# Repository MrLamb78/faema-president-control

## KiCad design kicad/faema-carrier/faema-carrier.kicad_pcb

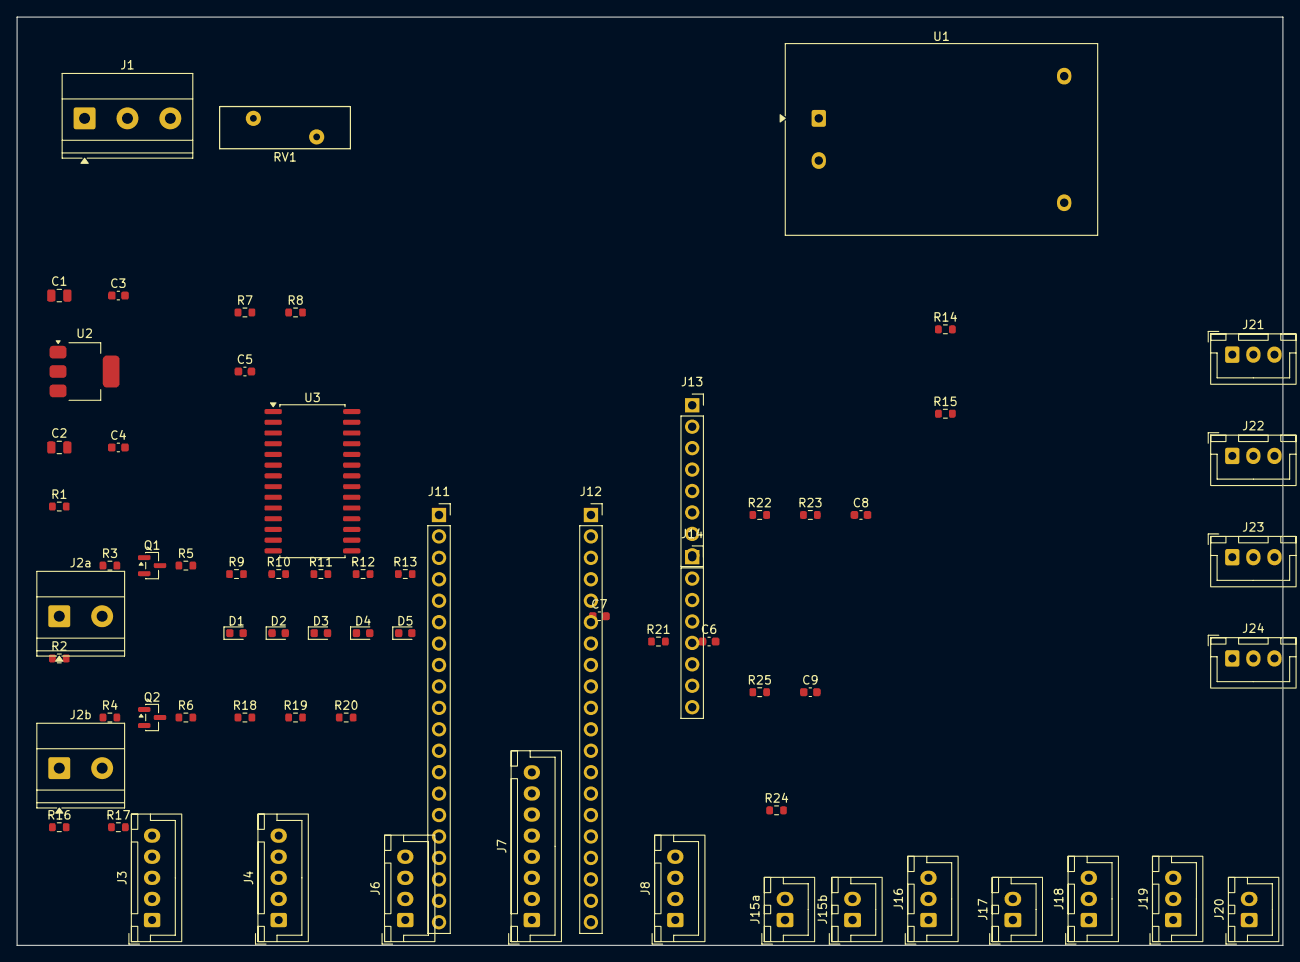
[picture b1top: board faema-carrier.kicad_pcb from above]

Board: 2 copper layers, 150.0 x 110.0 mm, 68 parts (0 on the bottom side), 59 nets, no tracks yet.

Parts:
C1, C2: 10uF_16V; C_0805_2012Metric
C3, C4, C5, C6, C7, C8: 100nF_50V; C_0603_1608Metric
C9: 10nF; C_0603_1608Metric
D1, D2, D3, D4, D5: GREEN; LED_0603_1608Metric
J1: AC_INPUT_220V; TerminalBlock_Phoenix_MKDS-1,5-3-5.08_1x03_P5.08mm_Horizont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
J2a: SSR1_OUT; TerminalBlock_Phoenix_MKDS-1,5-2-5.08_1x02_P5.08mm_Horizont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
J2b: SSR2_OUT; TerminalBlock_Phoenix_MKDS-1,5-2-5.08_1x02_P5.08mm_Horizont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
J3: ENCODER; JST_XH_B5B-XH-A_1x05_P2.50mm_Vertical
J4: BUTTONS; JST_XH_B5B-XH-A_1x05_P2.50mm_Vertical
J6: NEXTION; JST_XH_B4B-XH-A_1x04_P2.50mm_Vertical
J7: SPI_DISPLAY; JST_XH_B8B-XH-A_1x08_P2.50mm_Vertical
J8: I2C_RTC; JST_XH_B4B-XH-A_1x04_P2.50mm_Vertical
J11: PICO_L; PinSocket_1x20_P2.54mm_Vertical
J12: PICO_R; PinSocket_1x20_P2.54mm_Vertical
J13: RTD1; PinSocket_1x08_P2.54mm_Vertical
J14: RTD2; PinSocket_1x08_P2.54mm_Vertical
J15a: LEVEL1; JST_XH_B2B-XH-A_1x02_P2.50mm_Vertical
J15b: LEVEL2; JST_XH_B2B-XH-A_1x02_P2.50mm_Vertical
J16: FLOW; JST_XH_B3B-XH-A_1x03_P2.50mm_Vertical
J17: TEMP_AUX; JST_XH_B2B-XH-A_1x02_P2.50mm_Vertical
J18: PRESSURE; JST_XH_B3B-XH-A_1x03_P2.50mm_Vertical
J19: ANALOG_IN; JST_XH_B3B-XH-A_1x03_P2.50mm_Vertical
J20: PUMP_CTRL; JST_XH_B2B-XH-A_1x02_P2.50mm_Vertical
J21: OUT1; JST_XH_B3B-XH-A_1x03_P2.50mm_Vertical
J22: OUT2; JST_XH_B3B-XH-A_1x03_P2.50mm_Vertical
J23: OUT3; JST_XH_B3B-XH-A_1x03_P2.50mm_Vertical
J24: OUT4; JST_XH_B3B-XH-A_1x03_P2.50mm_Vertical
Q1, Q2: 2N7002; SOT-23
R1, R2: 220R; R_0603_1608Metric
R3, R4, R24: 100R; R_0603_1608Metric
R5, R6, R16, R18, R19, R20, R25: 10k; R_0603_1608Metric
R7, R8: 4k7; R_0603_1608Metric
R9, R10, R11, R12, R13: 470R; R_0603_1608Metric
R14, R15: 100k; R_0603_1608Metric
R17: 15k; R_0603_1608Metric
R21: 2k2_0.1%; R_0603_1608Metric
R22: 33k; R_0603_1608Metric
R23: 82k; R_0603_1608Metric
RV1: S14K275; RV_Disc_D15.5mm_W5mm_P7.5mm
U1: HLK-PM05; Converter_ACDC_Hi-Link_HLK-PMxx
U2: AMS1117-3.3; SOT-223-3_TabPin2
U3: MCP23017; SOIC-28W_7.5x17.9mm_P1.27mm

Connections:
+3V3: C2.1, C4.1, C5.1, C7.1, J3.4, J7.1, J8.1, J12.15, J13.1, J14.1, J19.1, J21.1, J22.1, J23.1, J24.1, R7.1, R8.1, R14.1, R15.1, R18.1, R19.1, R20.1, R21.1, R25.1, U2.2, U3.9, U3.11, U3.19
+5V: C1.1, C3.1, J6.1, J12.19, J16.1, J18.1, R1.1, R2.1, U1.3, U2.3
AC_L1_FUSED: J1.1, RV1.1, U1.1
AC_L2_FUSED: J1.2, RV1.2, U1.2
ANALOG_IN: J12.14, J19.2
BTN1: J4.1, U3.27
BTN2: J4.2, U3.26
BTN3: J4.3, U3.25
BTN4: J4.4, U3.24
BTN5: J4.5, U3.23
CS_DISP: J7.3, J11.14
CS_RTD1: J11.7, J13.7
CS_RTD2: J11.9, J14.7
DC_DISP: J7.5, J11.15
DISP_LED: J7.8, J11.17
ENC_CLK: J3.1, J12.1, R18.2
ENC_DT: J3.2, J12.2, R19.2
ENC_SW: J3.3, J12.4, R20.2
GATE1_DRIVE: Q1.1, R3.2, R5.1
GATE2_DRIVE: Q2.1, R4.2, R6.1
GND: C1.2, C2.2, C3.2, C4.2, C5.2, C6.2, C7.2, C8.2, C9.2, D1.2, D2.2, D3.2, D4.2, D5.2, J3.5, J6.2, J7.2, J8.2, J11.3, J11.8, J11.13, J11.18, J12.3, J12.8, J12.13, J12.18, J13.2, J14.2, J15a.2, J15b.2, J16.3, J17.2, J18.3, J19.3, J20.2, J21.3, J22.3, J23.3, J24.3, Q1.2, Q2.2, R5.2, R6.2, R17.2, R23.2, U1.4, U2.1, U3.10, U3.14, U3.15, U3.16
I2C_SCL: J8.4, J11.20, R8.2, U3.12
I2C_SDA: J8.3, J11.19, R7.2, U3.13
LED1: R9.1, U3.5
LED1_A: D1.1, R9.2
LED2: R10.1, U3.6
LED2_A: D2.1, R10.2
LED3: R11.1, U3.7
LED3_A: D3.1, R11.2
LED4: R12.1, U3.8
LED4_A: D4.1, R12.2
LED5: R13.1, U3.20
LED5_A: D5.1, R13.2
LEVEL1: J15a.1, R14.2, U3.22
LEVEL2: J15b.1, R15.2, U3.21
MCP_INT: J12.9, U3.17
OUT1: J21.2, U3.1
OUT2: J22.2, U3.2
OUT3: J23.2, U3.3
OUT4: J24.2, U3.4
PRESSURE: C8.1, J12.12, R22.2, R23.1
PRESSURE_RAW: J18.2, R22.1
PULSE_IN: C9.1, J12.7, J16.2, R25.2
PUMP_CTRL: J12.6, R24.1
PUMP_OUT: J20.1, R24.2
RST_DISP: J7.4, J11.16
SPI_MISO: J11.6, J13.5, J14.5
SPI_MOSI: J7.6, J11.5, J11.12, J13.6, J14.6
SPI_SCK: J7.7, J11.4, J11.11, J13.4, J14.4
SSR1_CTRL: J11.10, R3.1
SSR1_CTRL_P: J2a.1, R1.2
SSR1_DRIVE: J2a.2, Q1.3
SSR2_CTRL: J12.5, R4.1
SSR2_CTRL_P: J2b.1, R2.2
SSR2_DRIVE: J2b.2, Q2.3
TEMP_AUX: C6.1, J12.11, J17.1, R21.2
UART_RX: J11.2, R16.2, R17.1
UART_RX_5V: J6.3, R16.1
UART_TX: J6.4, J11.1

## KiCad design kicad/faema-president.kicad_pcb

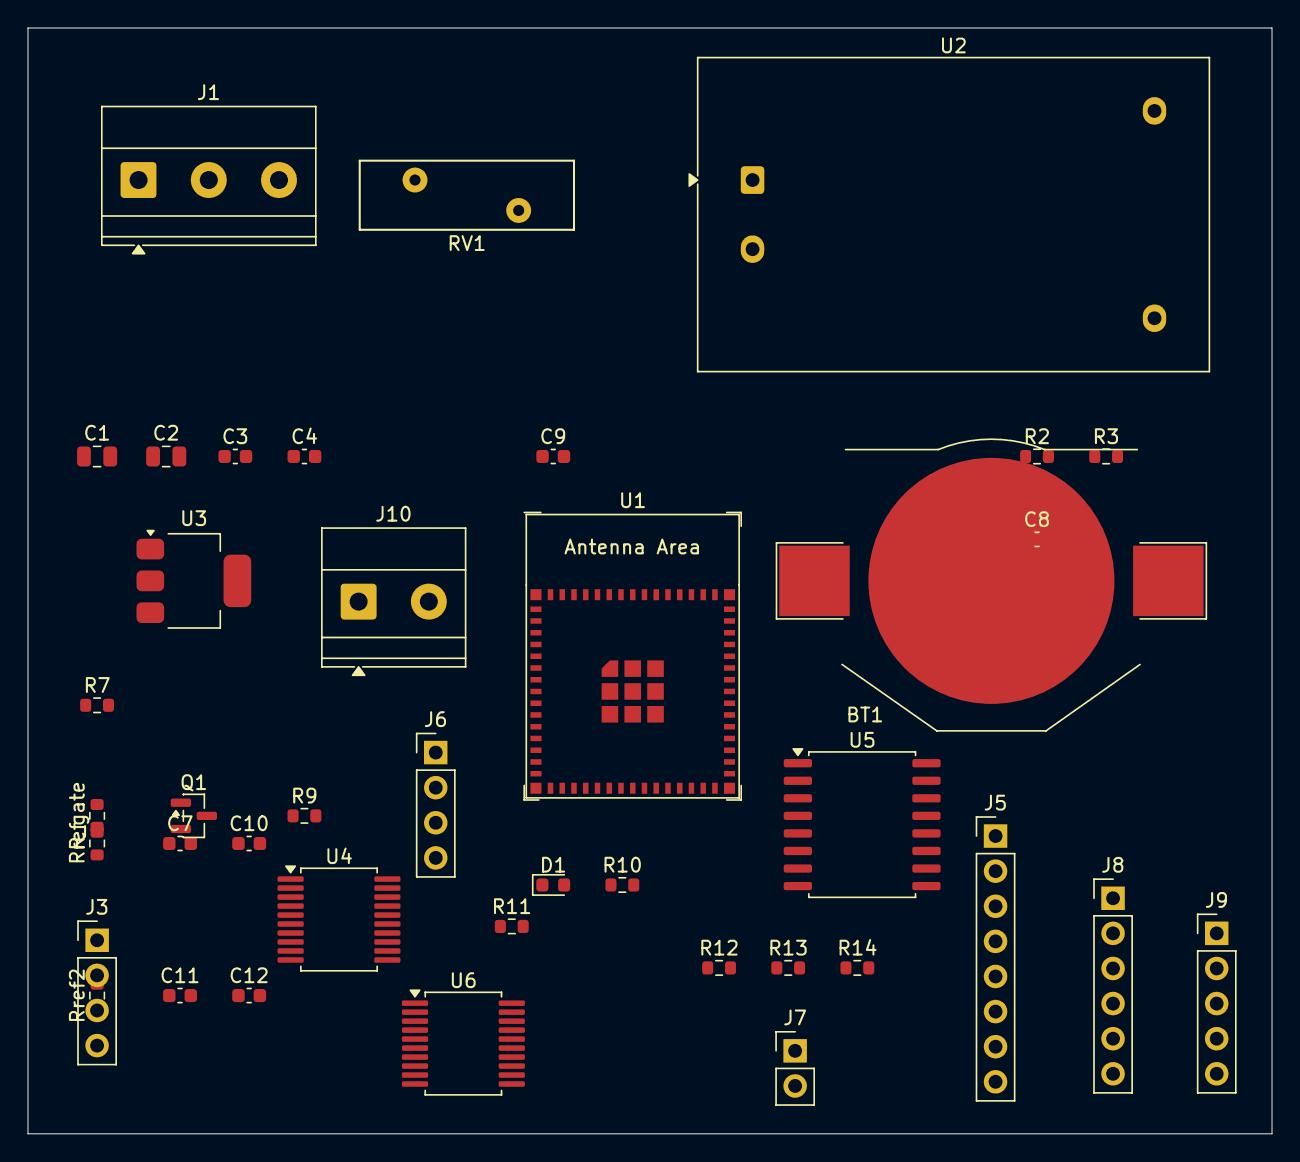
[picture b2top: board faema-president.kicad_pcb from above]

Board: 2 copper layers, 90.0 x 80.0 mm, 40 parts (0 on the bottom side), 40 nets, no tracks yet.

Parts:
BT1: CR2032; BatteryHolder_Keystone_3002_1x2032
C1: 10uF_16V_X5R; C_0805_2012Metric
C2: 10uF_10V_X5R; C_0805_2012Metric
C3, C4, C7, C8, C9, C10, C11, C12: 100nF_50V_X7R; C_0603_1608Metric
D1: LED_GREEN; LED_0603_1608Metric
J1: AC_INPUT_220V; TerminalBlock_Phoenix_MKDS-1,5-3-5.08_1x03_P5.08mm_Horizont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
J3: PT100_CALDEIRA; PinHeader_1x04_P2.54mm_Vertical
J5: ILI9341_2.4_HEADER; PinHeader_1x08_P2.54mm_Vertical
J6: PT100_GRUPO; PinHeader_1x04_P2.54mm_Vertical
J7: SONDA_NIVEL; PinHeader_1x02_P2.54mm_Vertical
J8: BOTOES_PRESET; PinHeader_1x06_P2.54mm_Vertical
J9: ENCODER_EC11; PinHeader_1x05_P2.54mm_Vertical
J10: SSR_CTRL_HEADER; TerminalBlock_Phoenix_MKDS-1,5-2-5.08_1x02_P5.08mm_Horizont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
Q1: 2N7002; SOT-23
R2, R3: 4k7_1pct; R_0603_1608Metric
R7: 220R_1pct; R_0603_1608Metric
R9, R12, R13, R14: 10k_1pct; R_0603_1608Metric
R10: 470R_1pct; R_0603_1608Metric
R11: 100k_1pct; R_0603_1608Metric
RV1: S14K275; RV_Disc_D15.5mm_W5mm_P7.5mm
R_gate: 100R_1pct; R_0603_1608Metric
Rref, Rref2: 430R_0.1pct; R_0603_1608Metric
U1: ESP32-S3-MINI-1-N8; ESP32-S3-MINI-1
U2: HLK-PM05; Converter_ACDC_Hi-Link_HLK-PMxx
U3: AMS1117-3.3; SOT-223-3_TabPin2
U4: MAX31865_CALDEIRA; SSOP-20_5.3x7.2mm_P0.65mm
U5: DS3231SN; SOIC-16W_7.5x10.3mm_P1.27mm
U6: MAX31865_GRUPO; SSOP-20_5.3x7.2mm_P0.65mm

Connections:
+3V3: C2.1, C4.1, C8.1, C9.1, C10.1, C12.1, J5.1, J5.8, J8.4, J9.4, R2.1, R3.1, R11.1, R12.1, R13.1, R14.1, U1.1, U1.25, U3.2, U4.1, U5.2, U5.5, U6.1
+5V: C1.1, C3.1, R7.1, U2.3, U3.3
AC_L1_FUSED: J1.1, RV1.1, U2.2
AC_L2_FUSED: J1.2, RV1.2, U2.1
BTN1: J8.1, R12.2, U1.19
BTN2: J8.2, R13.2, U1.20
BTN3: J8.3, R14.2, U1.21
CS_DISP: J5.3, U1.14
CS_MAX_CALD: U1.13, U4.2
CS_MAX_GRUPO: U1.18, U6.2
D1_A: D1.1, R10.2
DC_DISP: J5.5, U1.15
ENC_CLK: J9.1, U1.5
ENC_DT: J9.2, U1.6
ENC_SW: J9.3, U1.7
GND: BT1.2, C1.2, C2.2, C3.2, C4.2, C8.2, C9.2, C10.2, C12.2, D1.2, J1.3, J5.2, J7.2, J8.5, J8.6, J9.5, Q1.1, R9.2, U1.2, U2.4, U3.1, U4.9, U5.4, U6.9
I2C_SCL: R3.2, U1.9, U5.16
I2C_SDA: R2.2, U1.8, U5.15
LED_STATUS: R10.1, U1.22
LEVEL_SENSE: J7.1, R11.2, U1.17
MAX_DRDY: U1.3, U4.6
PT100_CALD_FN: J3.4, Rref.2, U4.8, U4.13
PT100_CALD_FP: J3.1, U4.7
PT100_CALD_RN: C7.2, J3.3, U4.11
PT100_CALD_RP: C7.1, J3.2, U4.10
PT100_GRUP_FN: J6.4, Rref2.2, U6.8, U6.13
PT100_GRUP_FP: J6.1, U6.7
PT100_GRUP_RN: C11.2, J6.3, U6.11
PT100_GRUP_RP: C11.1, J6.2, U6.10
Q1_GATE: Q1.2, R9.1, R_gate.2
RREF_CALD_P: Rref.1, U4.12
RREF_GRUP_P: Rref2.1, U6.12
RST_DISP: J5.4, U1.16
SPI_MISO: U1.12, U4.4, U6.4
SPI_MOSI: J5.6, U1.11, U4.3, U6.3
SPI_SCK: J5.7, U1.10, U4.5, U6.5
SSR_CTRL: R_gate.1, U1.4
SSR_CTRL_P: J10.1, R7.2
SSR_DRIVE: J10.2, Q1.3
VBAT: BT1.1, U5.14

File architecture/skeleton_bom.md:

# Faema President Control — Skeleton BOM

**Circuit:** `faema_president_control`
**Revision:** Rev.4 (SKiDL migration)
**Status:** skeleton — part-sourcer will validate stock, pricing, and exact LCSC PNs in the next stage.

Columns:
- **Refdes** — from SPEC §5 (locked)
- **Function** — block / role
- **Value / MPN** — architect's intent
- **Package** — footprint target
- **Qty** — in this design
- **Sourcing tier** — desired JLC tier (Basic / Preferred / Extended / non-LCSC)
- **Notes**

---

## Integrated circuits and modules

| Refdes | Function | Value / MPN | Package | Qty | Tier | Notes |
|--------|----------|-------------|---------|-----|------|-------|
| U1 | MCU module | ESP32-S3-MINI-1-N8 | Module 27x15 mm | 1 | Extended | Espressif; native USB; MicroPython |
| U2 | AC/DC 5 V isolated | HLK-PM05 | THT brick | 1 | Non-LCSC | User-soldered; 3 kV isolation |
| U3 | LDO 3.3 V | AMS1117-3.3 | SOT-223 | 1 | Basic | 1 W dissipation; needs thermal pour |
| U4 | RTD-to-digital (boiler) | MAX31865AAP+ | SSOP-20 | 1 | Extended | 4-wire, 50 Hz filter |
| U5 | RTC | DS3231SN# | SOIC-16W | 1 | Extended | ±2 ppm, I2C 0x68 |
| U6 | RTD-to-digital (group) | MAX31865AAP+ | SSOP-20 | 1 | Extended | same as U4 |

## Resistors

| Refdes | Value | Tolerance | Package | Qty | Tier | Role |
|--------|-------|-----------|---------|-----|------|------|
| Rref   | 430 Ω | 0.1 % 25 ppm | 0603 | 1 | Preferred | MAX31865 U4 reference |
| Rref2  | 430 Ω | 0.1 % 25 ppm | 0603 | 1 | Preferred | MAX31865 U6 reference |
| R2     | 4.7 kΩ | 1 % | 0603 | 1 | Basic | I2C SDA pull-up |
| R3     | 4.7 kΩ | 1 % | 0603 | 1 | Basic | I2C SCL pull-up |
| R7     | 100 Ω | 1 % | 0603 | 1 | Basic | SSR series current-limit |
| R9     | 10 kΩ | 1 % | 0603 | 1 | Basic | SSR pull-down (boot-safe) |
| R10    | 470 Ω | 1 % | 0603 | 1 | Basic | LED_STATUS current-limit |
| R11    | 100 kΩ | 1 % | 0603 | 1 | Basic | Level-probe pull-up |
| R12    | 10 kΩ | 1 % | 0603 | 1 | Basic | BTN1 pull-up |
| R13    | 10 kΩ | 1 % | 0603 | 1 | Basic | BTN2 pull-up |
| R14    | 10 kΩ | 1 % | 0603 | 1 | Basic | BTN3 pull-up |

Subtotal resistors: **11 pcs** across 7 distinct values.

## Capacitors

| Refdes | Value | Voltage | Dielectric | Package | Qty | Tier | Role |
|--------|-------|---------|------------|---------|-----|------|------|
| C1 | 10 µF | 16 V | X5R/X7R | 0805 | 1 | Basic | +5 V bulk at HLK-PM05 output |
| C2 | 10 µF | 10 V | X5R/X7R | 0805 | 1 | Basic | +3V3 bulk at AMS1117 output |
| C3 | 100 nF | 50 V | X7R | 0603 | 1 | Basic | +5 V ceramic at U3 input |
| C4 | 100 nF | 50 V | X7R | 0603 | 1 | Basic | +3V3 ceramic at U3 output |
| C7 | 100 nF | 50 V | X7R | 0603 | 1 | Basic | U4 RTDIN filter |
| C8 | 100 nF | 50 V | X7R | 0603 | 1 | Basic | DS3231 VCC bypass |
| C9 | 100 nF | 50 V | X7R | 0603 | 1 | Basic | ESP32 VDD bypass |
| C10 | 100 nF | 50 V | X7R | 0603 | 1 | Basic | U4 VDD bypass |
| C11 | 100 nF | 50 V | X7R | 0603 | 1 | Basic | U6 RTDIN filter |
| C12 | 100 nF | 50 V | X7R | 0603 | 1 | Basic | U6 VDD bypass |

Subtotal capacitors: **10 pcs** — collapse identical SKUs:
- 10 µF 0805: 2 pcs (C1, C2)
- 100 nF 0603 X7R: 8 pcs (C3, C4, C7–C12)

## Diodes / LEDs

| Refdes | Part | Package | Qty | Tier | Role |
|--------|------|---------|-----|------|------|
| D1 | Green LED 2 V | 0603 | 1 | Basic | Status indicator |

## Protection / safety

| Refdes | Part | Package | Qty | Tier | Role |
|--------|------|---------|-----|------|------|
| F1 | T16A slow-blow fuse | 5x20 mm glass + holder | 1 | Non-LCSC | AC input fuse |
| RV1 | S14K275 MOV | Disc radial THT | 1 | Non-LCSC | AC surge protection |

## Connectors / mechanical

| Refdes | Part | Package | Qty | Tier | Role |
|--------|------|---------|-----|------|------|
| J1 | 3-way screw terminal, 5.08 mm pitch | THT | 1 | Non-LCSC | L / N / PE in |
| J3 | 4-pin header, 2.54 mm | THT | 1 | Basic | Boiler PT100 (off-board) |
| J5 | 24-pin FPC 0.5 mm | SMD | 1 | Preferred | GC9A01 display ribbon |
| J6 | 4-pin header, 2.54 mm | THT | 1 | Basic | Group PT100 (off-board) |
| J7 | 2-pin header, 2.54 mm | THT | 1 | Basic | Level probe |
| J8 | 6-pin header, 2.54 mm | THT | 1 | Basic | Preset buttons panel |
| J9 | 2-pin screw terminal, 5.08 mm | THT | 1 | Non-LCSC | SSR output to boiler (optional on-board header) |
| ENC1 | EC11 rotary encoder + push | 5-pin THT | 1 | Non-LCSC | User input |
| BT1 | CR2032 battery holder | THT | 1 | Preferred | DS3231 backup |
| SSR1 | Fotek SSR-40DA | External | 1 | Non-LCSC | Not on PCB — header only |

## Totals

| Category | Distinct SKUs | Total pcs |
|----------|----------------|-----------|
| ICs / modules | 6 | 6 |
| Resistors | 7 distinct values | 11 |
| Capacitors | 2 distinct SKUs | 10 |
| LEDs / diodes | 1 | 1 |
| Protection | 2 | 2 |
| Connectors + mechanical | 9 | 10 (plus off-PCB SSR1) |
| **Grand total** | **~29 SKUs** | **~42 parts on PCB** |

---

## Open questions for the part-sourcer

1. **MAX31865 stock** — confirm at least 2 pcs available at LCSC with reasonable price (< $8 each). If out of stock, escalate to the architect (MAX31865 has no drop-in substitute in this architecture).
2. **430 Ω 0.1 % 25 ppm 0603** — verify LCSC has Preferred-tier stock for 2 pcs. A 0.1 % part is a hard requirement; do NOT substitute with 1 %.
3. **100 nF 400 V AC X1/X2 radial safety cap** — LCSC stocks a handful; pick the cheapest in-stock one with X1/Y2 or X2 rating. If nothing suitable, leave the footprint and flag for user hand-sourcing.
4. **S14K275 MOV** and **T16A fuse holder** — typically non-LCSC; sourcer may simply stub these to "user-source" in the final BOM, as they are hand-soldered.
5. **CR2032 holder** — pick the lowest-cost THT holder in LCSC Preferred (Keystone 1066, BAT-HLD-001 equivalent, etc.).
6. **ESP32-S3-MINI-1-N8** — verify current LCSC stock; if low, flag but do not substitute (architecture depends on this exact module pinout).

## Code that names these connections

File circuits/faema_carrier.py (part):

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

# ---------------------------------------------------------------------------
# BLOCK 5 — Level probes (LEVEL1/LEVEL2 — pull-ups, JST XH 2-pin)
# ---------------------------------------------------------------------------
@subcircuit
def block_level_probes():
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# ---------------------------------------------------------------------------
@subcircuit
def block_analog():
    """J19 (JST XH 3-pin): potentiometer wiper → ANALOG_IN (GP28/ADC2).
    J20 (JST XH 2-pin): PUMP_CTRL 0–3.3V → MGFR pump control input.
    R24 (100R): output series resistor on PUMP_CTRL for protection."""

    j19 = _JXH3()
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# ---------------------------------------------------------------------------
@subcircuit
def block_relay_outputs():
    """J21–J24 (JST XH 3-pin): MCP23017 OUT1–4 for external relay boards.
    Each connector: pin1=VCC(3V3 logic), pin2=SIGNAL, pin3=GND."""

    for i, net in enumerate([OUT1, OUT2, OUT3, OUT4], start=1):
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    j11 = _PS20()
    j11.ref = 'J11'
    j11.value = 'PICO_L'
    j11[1]  += UART_TX        # GP0  (pin 1)
    j11[2]  += UART_RX        # GP1  (pin 2) — 3.0V from divider
    j11[3]  += GND            #       (pin 3)
    j11[4]  += SPI_SCK        # GP2  (pin 4)
    j11[5]  += SPI_MOSI       # GP3  (pin 5)
    j11[6]  += SPI_MISO       # GP4  (pin 6)
    j11[7]  += CS_RTD1        # GP5  (pin 7)
    j11[8]  += GND            #       (pin 8)
    j11[9]  += CS_RTD2        # GP6  (pin 9)
    j11[10] += SSR1_CTRL      # GP7  (pin 10)
    j11[11] += SPI_SCK        # GP8  (pin 11) — SPI1 SCK, tied to SPI0 SCK for shared bus
    j11[12] += SPI_MOSI       # GP9  (pin 12) — SPI1 MOSI, tied to SPI0 MOSI
    j11[13] += GND            #       (pin 13)
    j11[14] += CS_DISP        # GP10 (pin 14)
    j11[15] += DC_DISP        # GP11 (pin 15)
    j11[16] += RST_DISP       # GP12 (pin 16)
    j11[17] += DISP_LED       # GP13 (pin 17)
    j11[18] += GND            #       (pin 18)
    j11[19] += I2C_SDA        # GP14 (pin 19)
    j11[20] += I2C_SCL        # GP15 (pin 20)

    # J12: right side, Pico physical pins 21–40
    j12 = _PS20()
    j12.ref = 'J12'
    j12.value = 'PICO_R'
    j12[1]  += ENC_CLK        # GP16 (pin 21)
    j12[2]  += ENC_DT         # GP17 (pin 22)
    j12[3]  += GND            #       (pin 23)
    j12[4]  += ENC_SW         # GP18 (pin 24)
    j12[5]  += SSR2_CTRL      # GP19 (pin 25)
    j12[6]  += PUMP_CTRL      # GP20 (pin 26)
    j12[7]  += PULSE_IN       # GP21 (pin 27)
    j12[8]  += GND            #       (pin 28)
    j12[9]  += MCP_INT        # GP22 (pin 29)
    # j12[10] = RUN            (pin 30) — not connected
    j12[11] += TEMP_AUX       # GP26/ADC0 (pin 31)
    j12[12] += PRESSURE       # GP27/ADC1 (pin 32)
    j12[13] += GND            # AGND      (pin 33)
    j12[14] += ANALOG_IN      # GP28/ADC2 (pin 34)
    j12[15] += VCC3V3         # ADC_VREF  (pin 35) — AMS1117 3V3, ratiometric ref
    # j12[16] = 3V3_OUT        (pin 36) — Pico output, not tied to carrier 3V3
    # j12[17] = 3V3_EN         (pin 37) — not connected
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
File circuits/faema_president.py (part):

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
    u1['3V3']           += VCC3V3
    u1['GND']           += GND
    u1['GPIO10_SCK']    += SPI_SCK
    u1['GPIO11_MOSI']   += SPI_MOSI
    u1['GPIO12_MISO']   += SPI_MISO
    u1['GPIO13_CSMAX']  += CS_MAX_CALD
    u1['GPIO18_CSMAX2'] += CS_MAX_GRUPO
    u1['GPIO14_CSDISP'] += CS_DISP
    u1['GPIO15_DCDISP'] += DC_DISP
    u1['GPIO16_RSTDSP'] += RST_DISP
    u1['GPIO8_SDA']     += I2C_SDA
    u1['GPIO9_SCL']     += I2C_SCL
    u1['GPIO4_SSR']     += SSR_CTRL
    u1['GPIO3_DRDY']    += MAX_DRDY
    u1['GPIO17_LEVEL']  += LEVEL_SENSE
    u1['GPIO2_LED']     += LED_STATUS
    u1['GPIO5_ENCCLK']  += ENC_CLK
    u1['GPIO6_ENCDT']   += ENC_DT
    u1['GPIO7_ENCSW']   += ENC_SW
    u1['GPIO19_BTN1']   += BTN1
    u1['GPIO20_BTN2']   += BTN2
    u1['GPIO21_BTN3']   += BTN3
    u1['EN']            += VCC3V3   # EN puxado para VCC via pull-up interno
    u1['USB_DP']        += NC(drive=True)
    u1['USB_DN']        += NC(drive=True)
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    r_gate = _R()
    r_gate.ref   = 'R_gate'
    r_gate.value = '100R_1pct'
    r_gate[1] += SSR_CTRL      # GPIO4
    r_gate[2] += Q1_GATE

    # R9 — pull-down 10 kΩ: mantém Q1 desligado durante boot/reset do ESP32
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
    j5[1] += VCC3V3     # VCC
    j5[2] += GND        # GND
    j5[3] += CS_DISP    # CS   — GPIO14
    j5[4] += RST_DISP   # RST  — GPIO16
    j5[5] += DC_DISP    # DC   — GPIO15
    j5[6] += SPI_MOSI   # MOSI — GPIO11
    j5[7] += SPI_SCK    # SCK  — GPIO10
    j5[8] += VCC3V3     # LED (backlight sempre ligado via 3V3)


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def block_ui():
    """J9 (encoder off-board), J8 (botões preset), D1 (LED), R10/R12/R13/R14"""

    # J9 — encoder EC11 off-board (5-pin header: ENC_CLK/ENC_DT/ENC_SW/3V3/GND)
    j9 = _Conn5()
    j9.ref   = 'J9'
    j9.value = 'ENCODER_EC11'
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    j9[4] += VCC3V3
    j9[5] += GND

    # J8 — painel de botões (6 pinos: BTN1/BTN2/BTN3 + 3V3 + GND + GND)
    j8 = _Conn6()
    j8.ref   = 'J8'
    j8.value = 'BOTOES_PRESET'
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
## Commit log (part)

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2026-04-13 modificações feita pelo Codex na geração do esquematico
